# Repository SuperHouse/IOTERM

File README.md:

I/O Breakout To Screw Terminals
===============================
Copyright 2017 SuperHouse Pty Ltd  
SuperHouse site:  www.superhouse.tv  

Breaks out a 2x6 pin header to 12 screw terminals.

Features:

 * 8 data lines
 * GND, VIN, IOREF, and RESET passed through

More information is available at:

  http://www.superhouse.tv/ioterm

INSTALLATION
------------
The design is saved as an EAGLE project. EAGLE PCB design software is
available from www.cadsoftusa.com free for non-commercial use. To use
this project download it and place the directory containing these files
into the "eagle" directory on your computer. Then open EAGLE and
navigate to the project.

DISTRIBUTION
------------
The specific terms of distribution of this project are governed by the
license referenced below.

LICENSE
-------
Licensed under the TAPR Open Hardware License (www.tapr.org/OHL).
The "license" folder within this repository also contains a copy of
this license in plain text format.

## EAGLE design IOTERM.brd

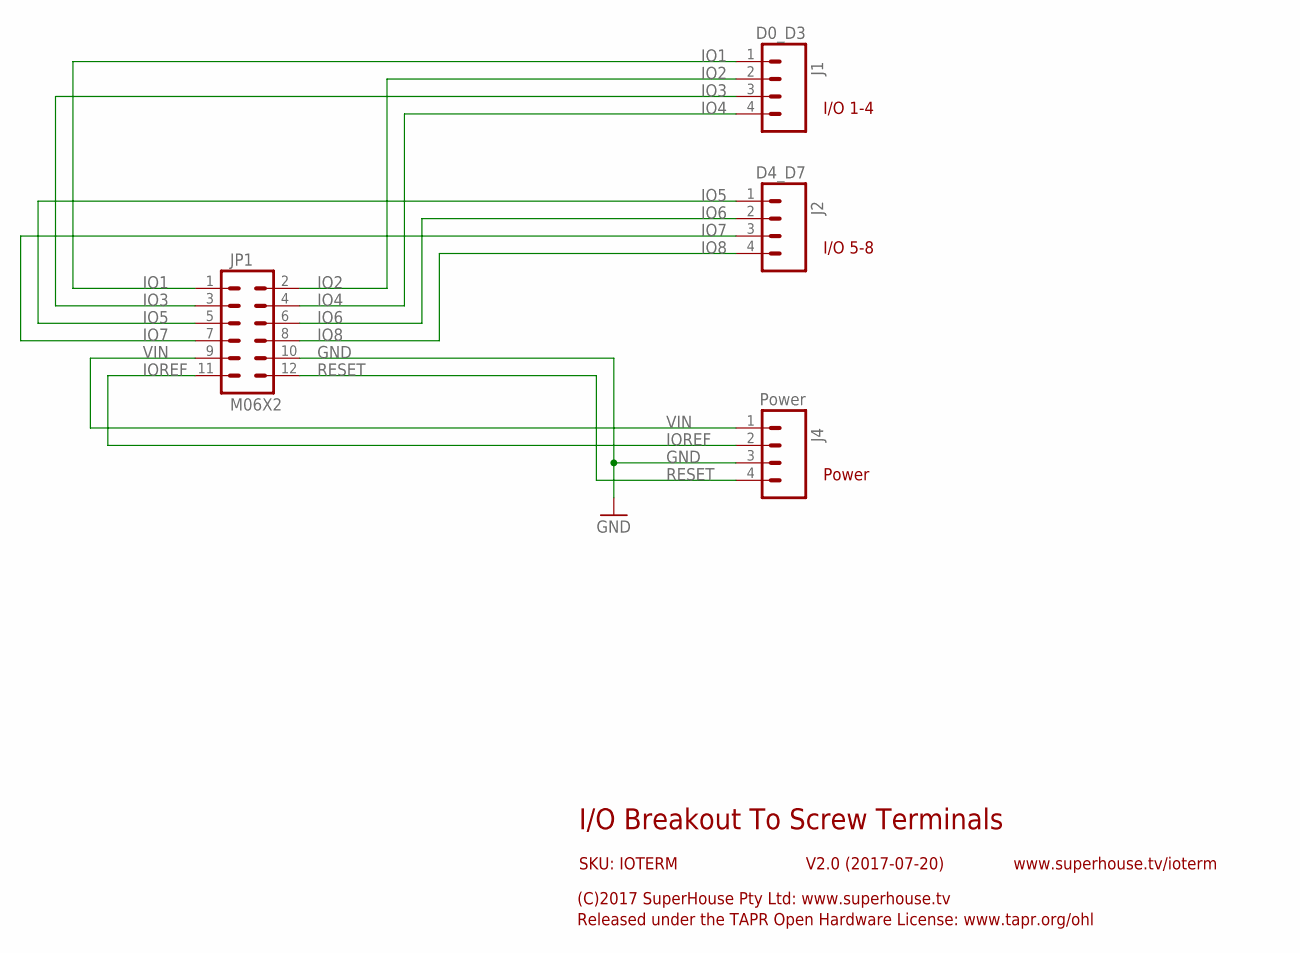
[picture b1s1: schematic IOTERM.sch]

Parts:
J1: D0_D3; SCREWTERMINAL-3.5MM-4
J2: D4_D7; SCREWTERMINAL-3.5MM-4
J4: Power; SCREWTERMINAL-3.5MM-4
JP1: M06X2; 2X6-SHROUDED

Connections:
GND: J4.3, JP1.10
IO1: J1.1, JP1.1
IO2: J1.2, JP1.2
IO3: J1.3, JP1.3
IO4: J1.4, JP1.4
IO5: J2.1, JP1.5
IO6: J2.2, JP1.6
IO7: J2.3, JP1.7
IO8: J2.4, JP1.8
IOREF: J4.2, JP1.11
RESET: J4.4, JP1.12
VIN: J4.1, JP1.9

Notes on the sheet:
I/O 1-4
I/O 5-8
I/O Breakout To Screw Terminals
V2.0 (2017-07-20)
SKU: IOTERM
(C)2017 SuperHouse Pty Ltd: www.superhouse.tv
Released under the TAPR Open Hardware License: www.tapr.org/ohl
www.superhouse.tv/ioterm
Power

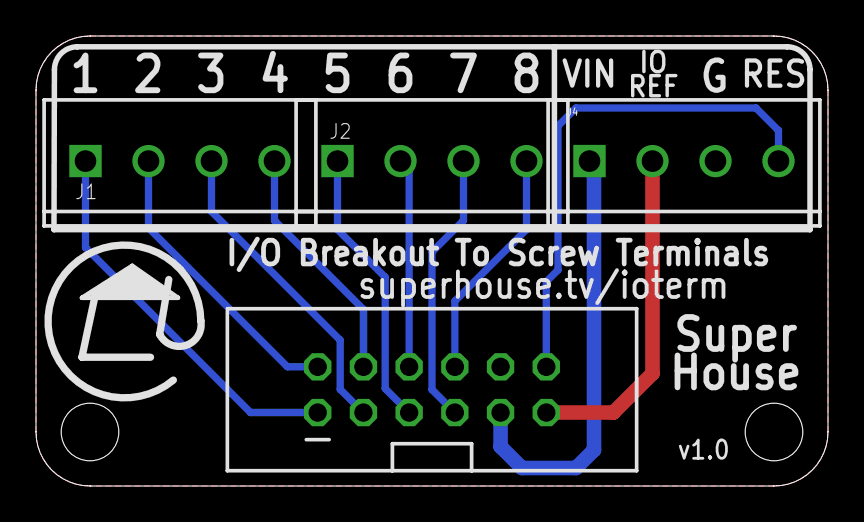
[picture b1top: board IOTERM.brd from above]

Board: 2 copper layers, 44.0 x 25.0 mm, 4 parts (0 on the bottom side), 12 nets.

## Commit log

2017-07-20 Initial import of files from IOBRSECSENSE project
2017-07-24 Expanded header to 2x6 for v2.0 release
2017-07-24 Updated README for v2.0 release
2017-07-25 Adjusted size to metric grid

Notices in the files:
IOTERM.brd:
(c) 2017 SuperHouse Automation Pty Ltd
